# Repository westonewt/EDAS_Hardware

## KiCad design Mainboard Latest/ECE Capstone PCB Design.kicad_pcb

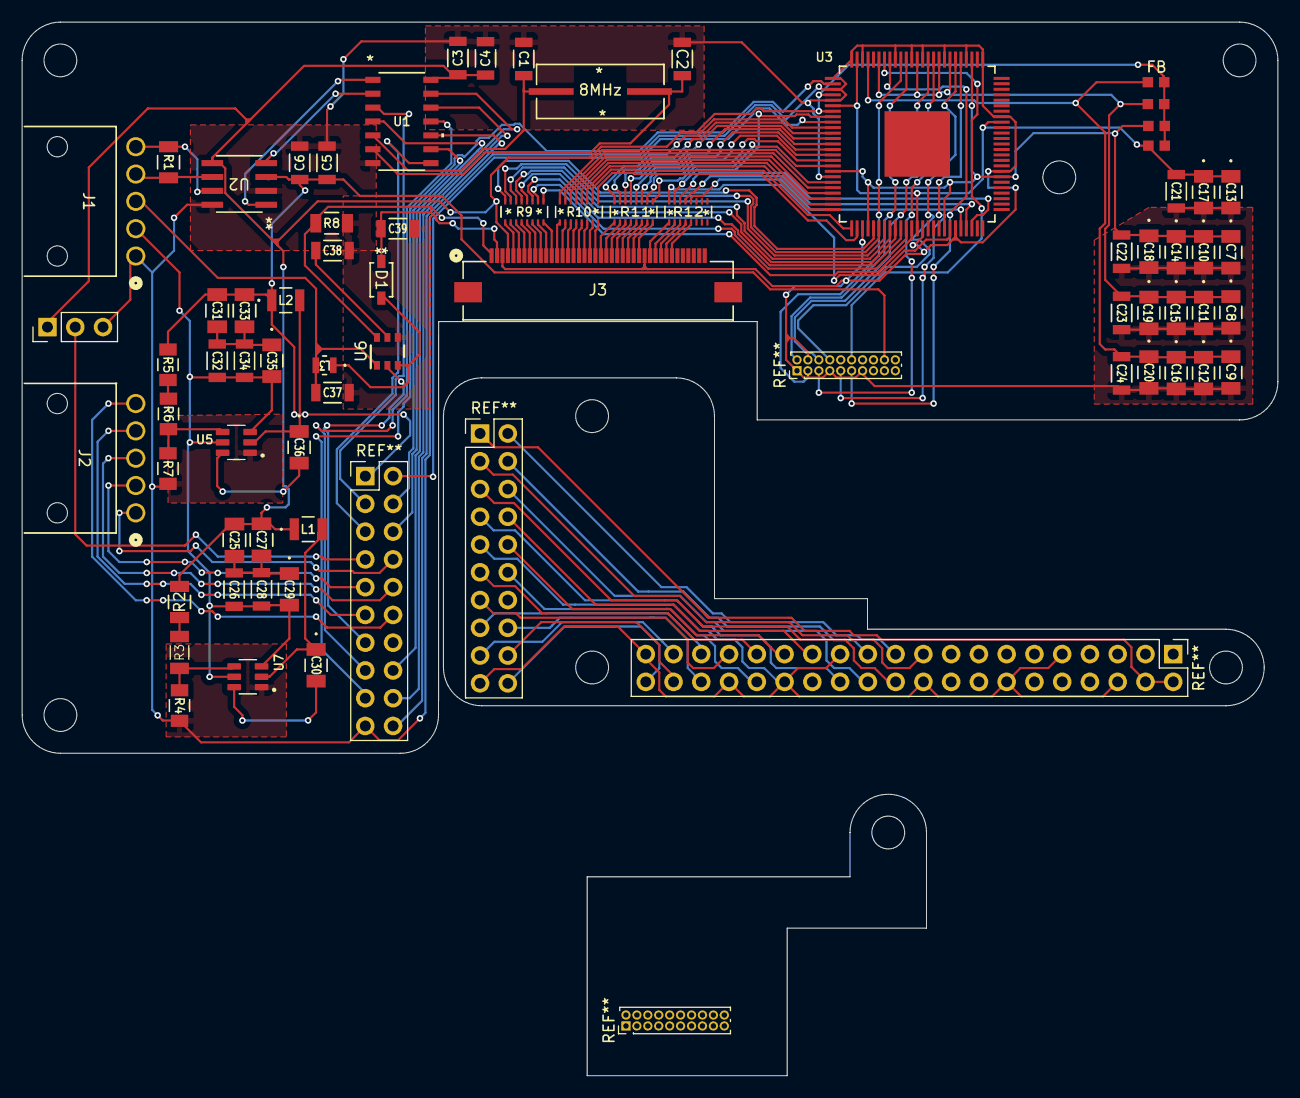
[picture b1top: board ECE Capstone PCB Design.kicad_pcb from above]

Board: 2 copper layers, 114.9 x 96.4 mm, 69 parts (0 on the bottom side), 80 nets.

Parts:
8MHz: 8MHz; ABLS-8.000MHZ-B2-T_ABR
C1, C2: 22pF; CAP_CL31_SAM
C3, C5, C21, C22, C23, C24, C26, C28, C32, C34: 10uF; CAP_CL31_SAM
C4, C6: 10nF; CAP_CL31_SAM
C7, C8, C9, C10, C11, C12, C13, C14, C15, C16, C17, C18, C19, C20, C29, C30, C35, C36: 0.1uF; CAP_1206_B_WAL
C25, C27, C31, C33: 22uF; CL1206_SAM
C37, C39: 4.7uF; CAP_CL31_SAM
C38: 220nF; CAP_CL31_SAM
D1: MBR0540; SOD-123_ONS
FB, FB1, FB2, FB4: BLM18RK601SN1D; FERRITE_0603_1P6XP8_MUR
J1, J2: 1053131105; CONN_SD-105313-100_05_MOL
J3: Conn_01x40_Socket; CONN40_CF3140_CVI
L1: 3.3uH; IND_TAIYO_LB3218_TAY
L2: 4.7uH; IND_TAIYO_LB3218_TAY
L3: 10uH; IND_TAIYO_LBR2012_TAY
R1: 120 ohm; STA_RMCF1206_STP
R2: 15k; STA_RMCF1206_STP
R3: 470; RESC3115X65N
R4, R6: 4.7k; RC1206N_YAG
R5: 33k; RC1206N_YAG
R7: 6.8k; RC1206N_YAG
R8: 5Ω; RES_CSRT1206FT5R00_STP
R9, R10, R11, R12: YC248-JR-07330RL; RES_YC248_4X1P6_YAG
U1: MCP2518FDT-H/SL; SOIC14_150MIL_SL_MCH
U2: MCP2542FD-E/SN; SOIC8_4P9X3P9MC_MCH
U3: QFP50P1600X1600X120-101N
U5, U7: TPS562201; SOT95P280X110-6N
U6: TPS61165DBV; DBV0006A_L

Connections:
7V: C26.2, C28.2, C29.2, C32.2, C34.2, C35.2, J1.2, U5.3 (VIN), U5.5 (EN), U7.3 (VIN), U7.5 (EN)
12V: C37.1, J1.3, L3.2, U6.1 (VIN)
+3.3V: C3.1, C4.1, C25.1, C25.2, C26.1, C27.1, C27.2, C28.1, C29.1, C31.2, C32.1, C33.2, C34.1, C35.1, FB.1, FB1.1, FB2.1, FB4.1, J3.4, L1.1, R2.2, U1.14 (VDD), U2.5 (VIO), U3.4 (PIXS), U3.7 (~STAG)
+5V: C5.1, C6.1, C31.1, C33.1, L2.1, R5.1, U2.3 (VDD)
/ACTIVE: J3.31, R12.2, R12.15, U3.8 (SCDT)
/B0: R11.16, U3.10 (QE0)
/B1: R11.15, U3.11 (QE1)
/B2: R11.14, U3.12 (QE2)
/B3: R11.13, U3.13 (QE3)
/B4: R11.12, U3.14 (QE4)
/B5: R11.11, U3.15 (QE5)
/B6: R11.10, U3.16 (QE6)
/B7: R11.9, U3.17 (QE7)
/CAN Bus connection H: J1.5, R1.1, U2.7 (CANH)
/CAN Bus connection L: J1.4, R1.2, U2.6 (CANL)
/DISPEN: J3.34, R12.5, R12.12, U3.46 (DE)
/G0: R10.16, U3.20 (QE8)
/G1: R10.15, U3.21 (QE9)
/G2: R10.14, U3.22 (QE10)
/G3: R10.13, U3.23 (QE11)
/G4: R10.12, U3.24 (QE12)
/G5: R10.11, U3.25 (QE13)
/G6: R10.10, U3.26 (QE14)
/G7: R10.9, U3.27 (QE15)
/GND: C1.1, C2.1, C3.2, C4.2, C5.2, C6.2, C7.2, C8.2, C9.2, C10.2, C11.2, C12.2, C13.2, C14.2, C15.2, C16.2, C17.2, C18.2, C19.2, C20.2, C21.2, C22.2, C23.2, C24.2, C37.2, C38.2, C39.2, J1.1, J3.3, J3.29, R4.2, R7.2, R8.2, U1.7 (VSS), U2.2 (VSS), U2.8 (STBY), U3.1 (DFO), U3.3 (ST), U3.5 (GND), U3.19 (OGND_3), U3.28 (OGND_5), U3.39 (GND_2), U3.45 (OGND), U3.58 (OGND_2), U3.68 (GND_3), U3.76 (OGND_4), U3.79 (AGND_2), U3.83 (AGND), U3.87 (AGND_5), U3.89 (AGND_3), U3.92 (AGND_4), U3.98 (PGND), U3.100 (OCK_INV), U5.1 (GND), U6.4 (GND), U7.1 (GND)
/HSYNC: J3.32, R12.3, R12.14, U3.48 (HSYNC)
/LEDA: C39.1, D1.1 (CATHODE), J3.2
/LEDK: J3.1, R8.1, U6.6 (FB)
/PIXCLK: J3.30, R12.1, R12.16, U3.44 (ODCK)
/R0: R9.16, U3.30 (QE16)
/R1: R9.15, U3.31 (QE17)
/R2: R9.14, U3.32 (QE18)
/R3: R9.13, U3.33 (QE19)
/R4: R9.12, U3.34 (QE20)
/R5: R9.11, U3.35 (QE21)
/R6: R9.10, U3.36 (QE22)
/R7: R9.9, U3.37 (QE23)
/RX: U1.2 (RXCAN), U2.4 (RXD)
/TX: U1.1 (TXCAN), U2.1 (TXD)
/VSYNC: J3.33, R12.4, R12.13, U3.47 (VSYNC)
unnamed: D1.2 (ANODE), L3.1, U6.3 (SW)
unnamed: J3.5, R9.1
unnamed: J2.2, J3.6, R9.2
unnamed: J2.3, J3.7, R9.3
unnamed: J2.4, J3.8, R9.4
unnamed: J2.5, J3.9, R9.5
unnamed: J3.10, R9.6
unnamed: J3.11, R9.7
unnamed: J3.12, R9.8
unnamed: J3.13, R10.1
unnamed: J3.14, R10.2
unnamed: J3.15, R10.3
unnamed: J3.16, R10.4
unnamed: J3.17, R10.5
unnamed: J3.18, R10.6
unnamed: J3.19, R10.7
unnamed: J3.20, R10.8
unnamed: J3.21, R11.1
unnamed: J3.22, R11.2
unnamed: J3.23, R11.3
unnamed: J3.24, R11.4
unnamed: J3.25, R11.5
unnamed: J3.26, R11.6
unnamed: J3.27, R11.7
unnamed: J3.28, R11.8
unnamed: R2.1, R3.2
unnamed: R5.2, R6.1
unnamed: 8MHz.2, C2.2, U1.6 (OSC1)
unnamed: 8MHz.1, C1.2, U1.5 (OSC2)
unnamed: C8.1, C11.1, C15.1, C19.1, C23.1, FB2.2, U3.82 (AVDD_2), U3.84 (AVDD), U3.88 (AVDD_3), U3.95 (AVDD_4)
unnamed: C13.1, C17.1, C21.1, FB4.2, U3.6 (DVDD_3), U3.38 (DVDD_2), U3.67 (DVDD), U3.99 (RSVD)
unnamed: C7.1, C10.1, C14.1, C18.1, C22.1, FB1.2, U3.18 (OVDD_5), U3.29 (OVDD_3), U3.43 (OVDD_2), U3.57 (OVDD_4), U3.78 (OVDD)
unnamed: C9.1, C12.1, C16.1, C20.1, C24.1, FB.2, U3.97 (PVDD)
unnamed: C36.1, L2.2, U5.2 (SW)
unnamed: C36.2, U5.6 (VBST)
unnamed: R6.2, R7.1, U5.4 (VFB)
unnamed: C38.1, U6.5 (COMP)
unnamed: C30.1, L1.2, U7.2 (SW)
unnamed: C30.2, U7.6 (VBST)
unnamed: R3.1, R4.1, U7.4 (VFB)

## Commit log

2025-01-16 Added initial kiCAD schematics
2025-02-07 Renamed folder
2025-02-07 Undone
2025-02-07 fixed
2025-02-09 Changed dev mode pin from 5V to 3.3V to comply with rasp pi high logic voltage. Changed some traces to remove any sharp angles and create more uniform lines where possible. Updated M2.5 screw cutouts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
2025-02-09 Fixed an issue with the dev mode pins connection to 3.3V rail
2025-02-09 Added 1mm to the bottom of the PCB where the rasp pi sits. Moved the ferrite beads to give more room around the screw mounts. Cleaned up the silk screen layer.
2025-02-09 Remove backup files and modifications to V1.1
2025-02-09 Cleaned up main branch
2025-02-12 Added the first daughter board. Added a model of the pi
2025-02-12 Completed pi daughter board. Dimensions should be accurate to 0.025mm. Placed it with the mainboard in such a way that it is configured for paneling
2025-02-12 Laid out HDMI daughter board. HDMI interconnect not finished yet. Added screw hole for HDMI daughterboard. Moved the display decoder capacitors further towards the right edge of the main board and re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
2025-02-15 Completed mainboard redesign and all daughter boards
2025-02-15 Final release of revision 0
2025-02-15 Cleaned up the directory
2025-02-15 Found a problem with one of the HDMI traces where the same net track spacing was to small. Corrected
2025-02-15 Updated main to match recovery-branch
2025-02-25 Fixed a whole bunch of issues with the silk screen. Created a new naming convention for the capacitors to reduce the amount of characters in the silk screen. Added thermal relief vias to all of the t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
